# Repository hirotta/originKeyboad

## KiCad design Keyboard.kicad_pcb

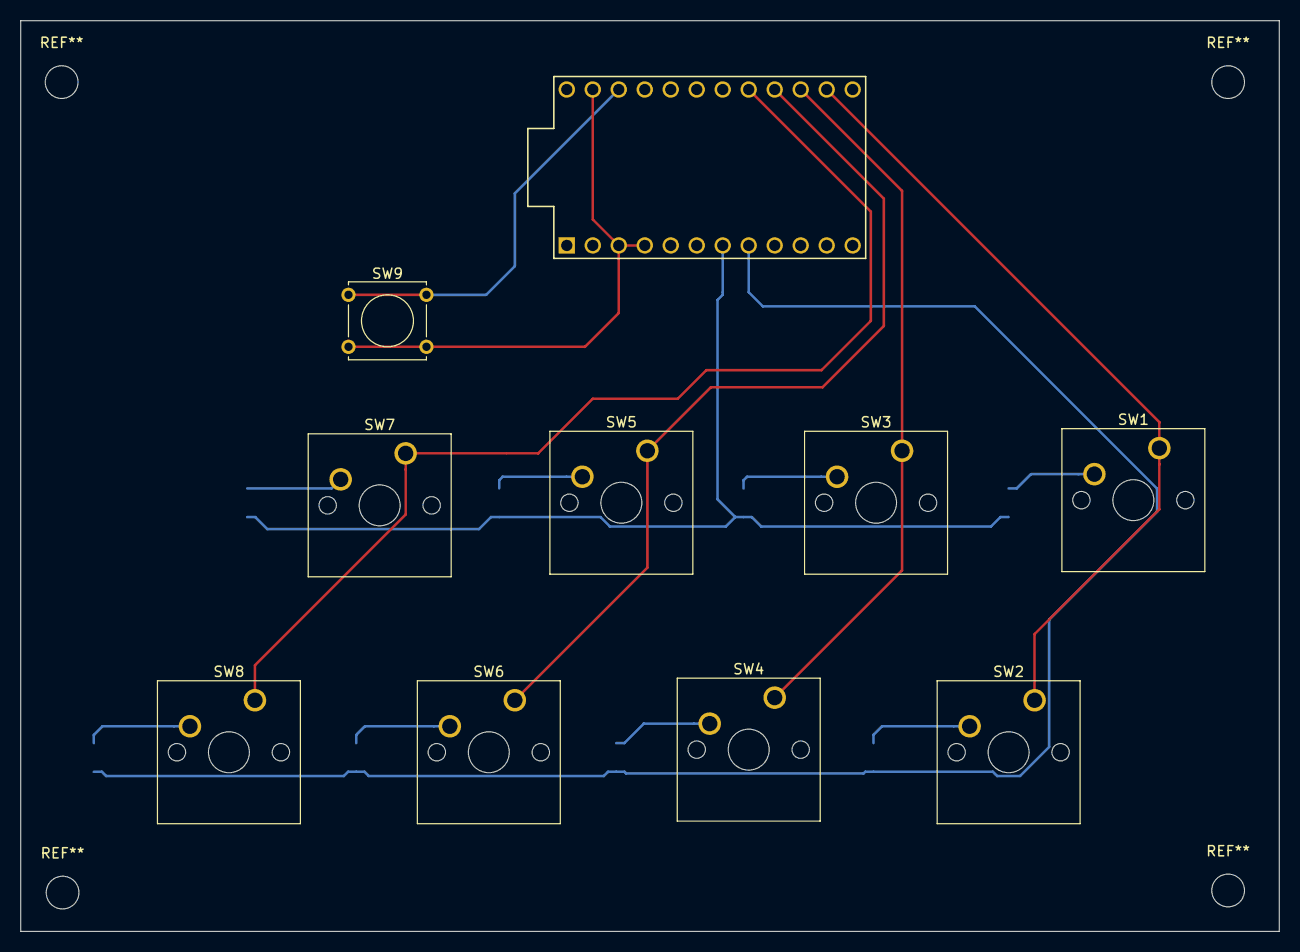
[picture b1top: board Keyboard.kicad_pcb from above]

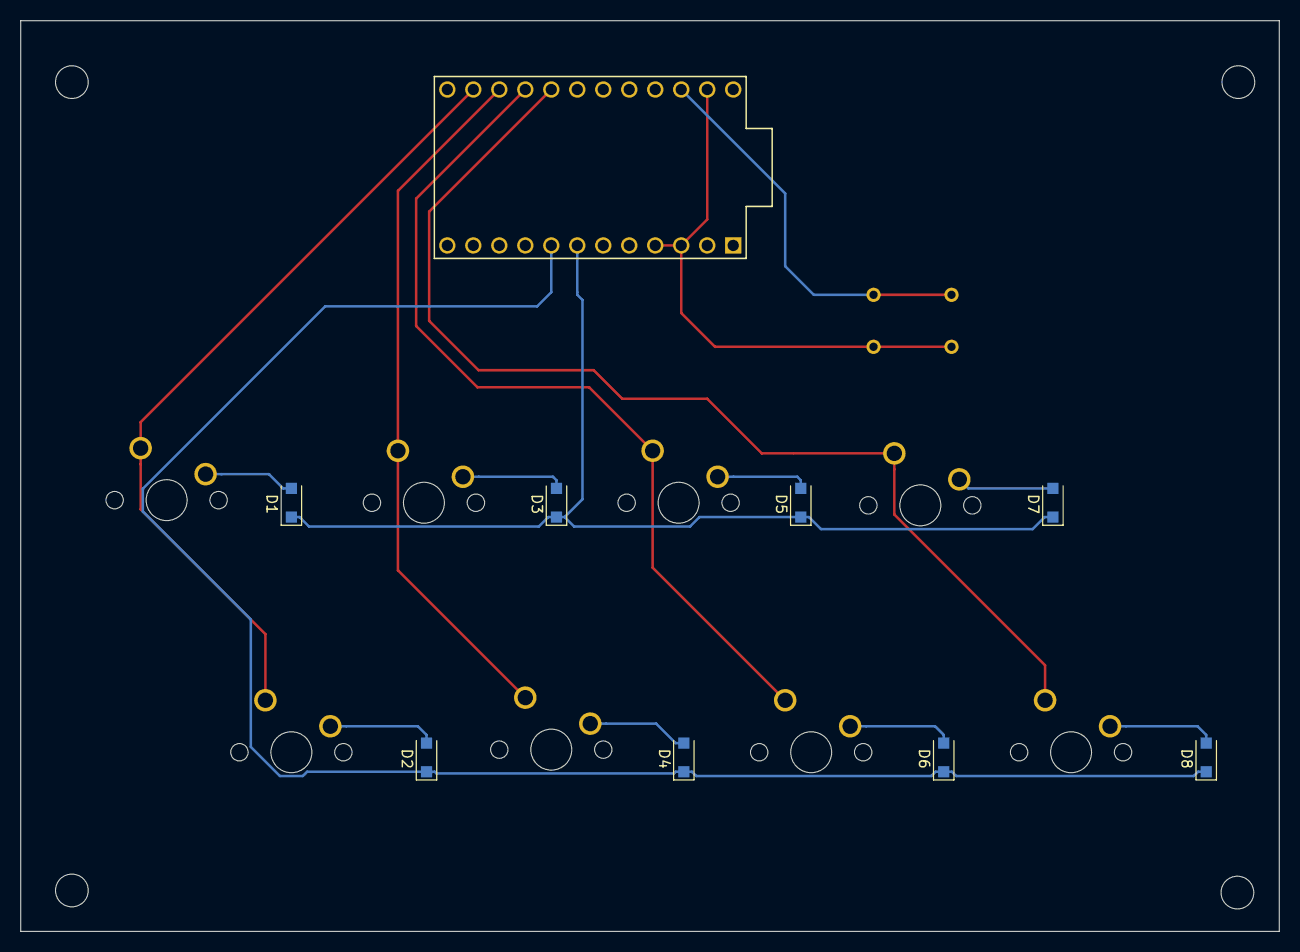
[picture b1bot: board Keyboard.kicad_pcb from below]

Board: 2 copper layers, 123.0 x 89.0 mm, 18 parts (8 on the bottom side), 16 nets.

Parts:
D1, D2, D3, D4, D5, D6, D7, D8: D; D_SOD-123F
SW1, SW2, SW3, SW4, SW5, SW6, SW7, SW8: SW_Push; SW_Cherry_MX_1.00u_PCB
SW9: SW_Push; SW_Tactile_Straight_KSA0Axx1LFTR
U1: ProMicro

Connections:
GND: SW9.2, U1.3, U1.4, U1.23
unnamed: D1.2, SW1.2
unnamed: D2.2, SW2.2
unnamed: D3.2, SW3.2
unnamed: D4.2, SW4.2
unnamed: D5.2, SW5.2
unnamed: D6.2, SW6.2
unnamed: D7.2, SW7.2
unnamed: D8.2, SW8.2
unnamed: SW9.1, U1.22
ROW0: D1.1, D3.1, D5.1, D7.1, U1.7
ROW1: D2.1, D4.1, D6.1, D8.1, U1.8
col0: SW1.1, SW2.1, U1.14
col1: SW3.1, SW4.1, U1.15
col2: SW5.1, SW6.1, U1.16
col3: SW7.1, SW8.1, U1.17

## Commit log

2019-11-16 microUSB circuit
